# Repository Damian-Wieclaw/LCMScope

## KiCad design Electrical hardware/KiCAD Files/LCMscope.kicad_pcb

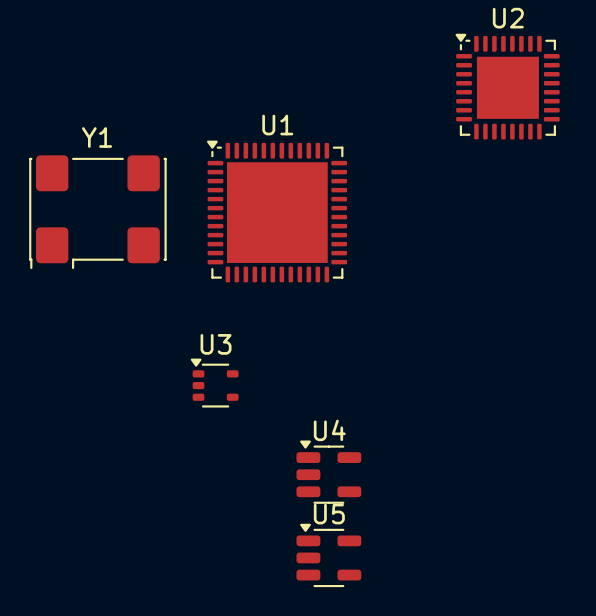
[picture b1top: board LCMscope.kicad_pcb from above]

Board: 2 copper layers, 6 parts (0 on the bottom side), 6 nets, no tracks yet.

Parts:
U1: ICE40UP5K-SG48ITR; QFN-48-1EP_7x7mm_P0.5mm_EP5.6x5.6mm
U2: LTC2254; QFN-32-1EP_5x5mm_P0.5mm_EP3.45x3.45mm
U3: MIC5365-3.3YC5; SOT-353_SC-70-5
U4: TLV70212_SOT23-5; SOT-23-5
U5: TLV73325PDBV; SOT-23-5
Y1: ASV-xxxMHz; Oscillator_SMD_Abracon_ASV-4Pin_7.0x5.1mm

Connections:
+2V5: U1.24 (VPP_2V5), U1.29 (VCCPLL), U5.5 (OUT)
+3.3V: U1.1 (VCCIO_2), U1.22 (SPI_VCCIO1), U1.33 (VCCIO_0), U3.5 (VOUT), U4.1 (IN), U5.1 (IN), Y1.4 (Vdd)
CLK(48MHz): U1.44 (IOB_3b_G6), Y1.3 (OUT)
GND: U1.49 (GND), U3.2 (GND), U4.2 (GND), U5.2 (GND), Y1.2 (GND)
unnamed: U1.5 (VCC), U1.30 (VCC)
unnamed: U2.17 (D5), U2.18 (D6)

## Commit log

2025-07-31 added hierarchical structure
2025-08-01 Created ADC footprint and extracted most important data from the data sheet
2025-08-01 Create README.md
    Added block diagram to readme
2025-08-01 Added pdf schematic and single ended to differential diagram on analog frontend page
2025-08-01 splited electircal hardware folder on PDF folder and KicadFIles
2025-08-03 added readme files for sw folders
2025-08-03 Added drawio diagram for later modifications
2025-08-03 Added toolchain block diagram
2025-08-03 Added state machine diagram for fpga
2025-08-03 Added drawio file
2025-08-05 adding voltage divider
